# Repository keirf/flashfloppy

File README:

FlashFloppy
===========
Keir Fraser <keir.xen@gmail.com>
https://github.com/keirf/flashfloppy

This distribution contains FlashFloppy custom firmware for Gotek and
Gotek-compatible hardware.

FlashFloppy documentation and downloads:
  https://github.com/keirf/flashfloppy/wiki/

Supported Microcontrollers
--------------------------
FlashFloppy supports two types of STM32-like microcontroller:
 STM32F105 (and the compatible AT32F415)
   - 72MHz Cortex-M3, 128kB Flash, 64kB RAM (AT32F415: 32kB RAM)
 AT32F435
   - 288MHz Cortex-M4, 256kB Flash, 384kB RAM

If you want to know which type of MCU you have, you can open your Gotek and
read the writing on the square chip on your Gotek PCB.

Firmware Programming
--------------------
If programming a factory-fresh Gotek running factory firmware, you will need
to program a HEX or DFU firmware file as explained in the wiki, linked above.
These files are located in the hex/ and dfu/ folders respectively, and you
must use the correct file for your microcontroller:
 STM32F105, AT32F415
   - Use file "dfu/flashfloppy-at415-st105-<ver>.dfu" (or .hex equivalent)
 AT32F435
   - Use file "dfu/flashfloppy-at435-<ver>.dfu" (or .hex equivalent)

Firmware Update
---------------
Once FlashFloppy has been flashed to a device (using a HEX or DFU file),
further updates can be made via an Update file on a USB drive, as described
in the wiki.

To support older versions of the FlashFloppy bootloader, two types of
Update file are included in the distribution, distinguishable by name:
 FF_Gotek-*.upd: Legacy Update file
    - All STM32F105/AT32F415 devices
 flashfloppy-*.upd: Universal Update file
    - All AT32F435 devices
    - STM32F105/AT32F415 devices running a recent FlashFloppy bootloader

Each update format will only work with a device (and FlashFloppy bootloader)
that supports it. If you are unsure which to use, it is okay to copy both
Update file types to your USB drive: the bootloader will correctly load just
one of the Update file types that it supports.

Alternatively try one Update file at a time, and switch to the other type if
you see error E01 on the Gotek display.

Alternative Firmwares
---------------------
In the alt/ folder you will find (pairs of) Update files implementing
alternative firmwares. Most users can ignore these, and use only the
Update files in the root of the distribution.

The alternative firmwares include:
 * alt/bootloader: Updates your Gotek bootloader
   - WARNING: Proceed with caution. Read the Firmware Update page on the wiki.
 * alt/io-test: Test your Gotek I/O pins if you suspect a hardware fault
 * alt/quickdisk: QuickDisk emulation (see the wiki)
   - If you don't know what QuickDisk is, you don't need this firmware.
 * alt/logfile: Firmware with debug logging to FFLOG.TXT on the USB drive
   - Useful only for fault finding. Not for general use.

Redistribution
--------------
Source code, and all binary releases, are freely redistributable in
any form. Please see the the COPYING file included in this
distribution.

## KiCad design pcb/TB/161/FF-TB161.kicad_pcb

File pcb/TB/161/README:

FF-TB161
--------
KiCad project for schematic and 10cmx5cm single-board layout.
Can be opened in the KiCad project manager.

FF-TB161-bom.txt
----------------
Bill of materials for the above design, excluding pin headers
and socket strips.

FF-TB161-panel
--------------
Two-up 10x10cm panelisation of the above layout, with cutouts
and break-away mousebites. Should be opened directly in Pcbnew.

Generating Gerbers
------------------
Nothing special to note here. Some of these options are important to
follow, especially for the drill file.
Options:
 Plot footprint values
 Plot footprint references
 Exclude PCB edge layer from other layers
Gerber Options:
 Use Protel filename extensions
 Format: 4.6
Drill files:
 Drill Units:    Inches
 Zeros Format:   Suppress leading zeros
 Precision:      2:4
 Drill Options:  Minimal header
 Drill Origin:   Absolute

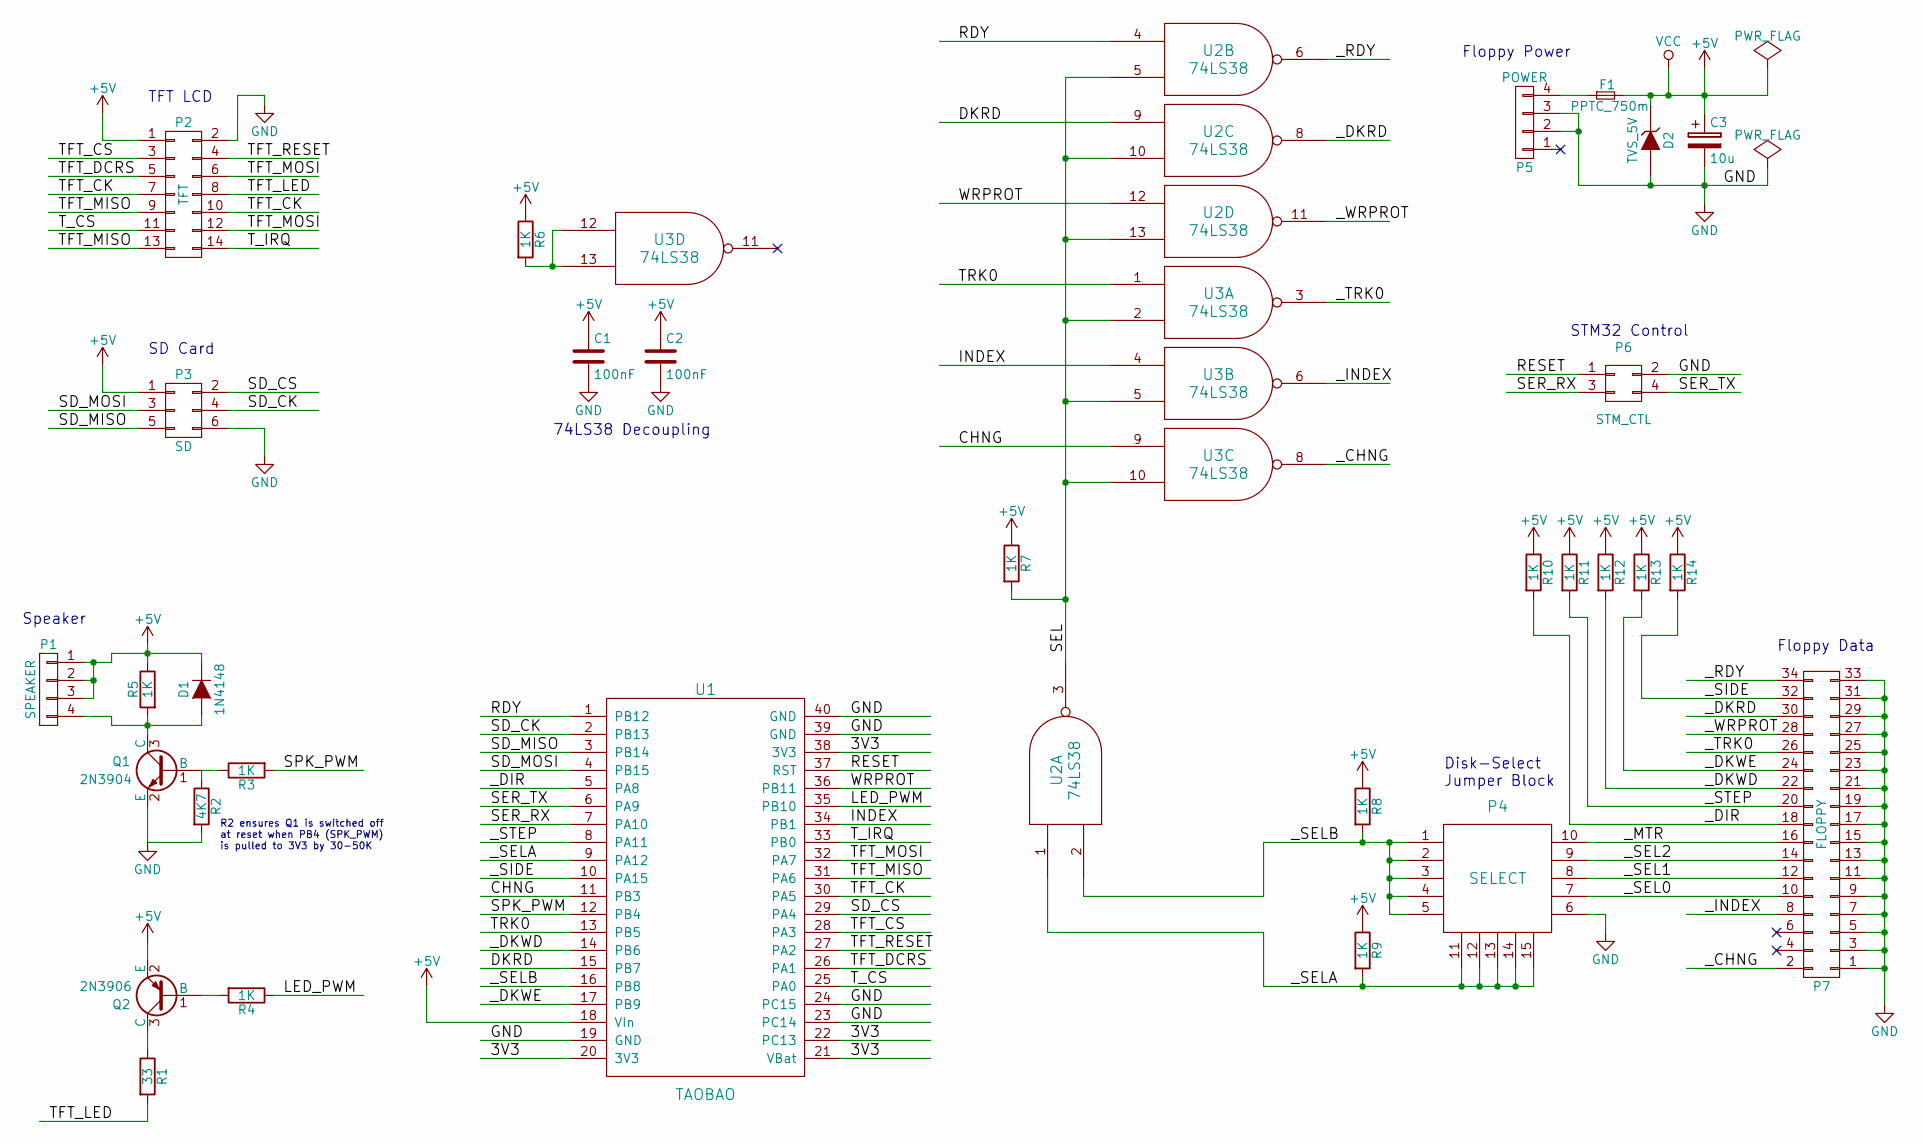
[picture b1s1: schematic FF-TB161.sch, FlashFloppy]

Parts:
C1, C2: 100nF; R_0805_HandSoldering
C3: 10u; C_3528
D1: 1N4148; MiniMELF_Handsoldering
D2: TVS_5V; D_SOD128
F1: PPTC_750m; R_0805_HandSoldering
P1: SPEAKER; Pin_Header_Straight_1x04
P2: TFT; Pin_Header_Straight_2x07
P3: SD; Pin_Header_Straight_2x03
P4: SELECT; Pin_Header_Straight_3x05
P5: POWER; Pin_Header_Straight_1x04
P6: STM_CTL; Pin_Header_Straight_2x02
P7: FLOPPY; Pin_Header_Straight_2x17
Q1: 2N3904; SOT-23_Handsoldering
Q2: 2N3906; SOT-23_Handsoldering
R1: 33; R_1206_HandSoldering
R2: 4K7; R_0805_HandSoldering
R3, R4, R5, R6, R7, R8, R9, R10, R11, R12, R13, R14: 1K; R_0805_HandSoldering
U1: TAOBAO; DIP-40_W15.24mm
U2, U3: 74LS38; SOIC-14_N

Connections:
+5V: C1.1, C2.1, C3.1, D1.1 (K), D2.1 (K), F1.2, P1.1, P1.2, P1.3, P2.1, P3.1, Q2.2 (E), R5.1, R6.1, R7.1, R8.1, R9.1, R10.1, R11.1, R12.1, R13.1, R14.1, U1.18 (VIn), U2.14 (VCC), U3.14 (VCC)
/3V3: U1.20 (3V3), U1.21 (VBat), U1.22 (PC13), U1.38 (3V3)
/CHNG: U1.11 (PB3), U3.9
/DKRD: U1.15 (PB7), U2.9
/INDEX: U1.34 (PB1), U3.4
/LED_PWM: R4.1, U1.35 (PB10)
/RDY: U1.1 (PB12), U2.4
/RESET: P6.1, U1.37 (RST)
/SD_CK: P3.4, U1.2 (PB13)
/SD_CS: P3.2, U1.29 (PA4)
/SD_MISO: P3.5, U1.3 (PB14)
/SD_MOSI: P3.3, U1.4 (PB15)
/SEL: R7.2, U2.3, U2.5, U2.10, U2.13, U3.2, U3.5, U3.10
/SER_RX: P6.3, U1.7 (PA10)
/SER_TX: P6.4, U1.6 (PA9)
/SPK_PWM: R3.2, U1.12 (PB4)
/TFT_CK: P2.7, P2.10, U1.30 (PA5)
/TFT_CS: P2.3, U1.28 (PA3)
/TFT_DCRS: P2.5, U1.26 (PA1)
/TFT_LED: P2.8, R1.2
/TFT_MISO: P2.9, P2.13, U1.31 (PA6)
/TFT_MOSI: P2.6, P2.12, U1.32 (PA7)
/TFT_RESET: P2.4, U1.27 (PA2)
/TRK0: U1.13 (PB5), U3.1
/T_CS: P2.11, U1.25 (PA0)
/T_IRQ: P2.14, U1.33 (PB0)
/WRPROT: U1.36 (PB11), U2.12
/_CHNG: P7.2, U3.8
/_DIR: P7.18, R10.2, U1.5 (PA8)
/_DKRD: P7.30, U2.8
/_DKWD: P7.22, R12.2, U1.14 (PB6)
/_DKWE: P7.24, R13.2, U1.17 (PB9)
/_INDEX: P7.8, U3.6
/_MTR: P4.10, P7.16
/_RDY: P7.34, U2.6
/_SEL0: P4.7, P7.10
/_SEL1: P4.8, P7.12
/_SEL2: P4.9, P7.14
/_SELA: P4.11, P4.12, P4.13, P4.14, P4.15, R9.2, U1.9 (PA12), U2.1
/_SELB: P4.1, P4.2, P4.3, P4.4, P4.5, R8.2, U1.16 (PB8), U2.2
/_SIDE: P7.32, R14.2, U1.10 (PA15)
/_STEP: P7.20, R11.2, U1.8 (PA11)
/_TRK0: P7.26, U3.3
/_WRPROT: P7.28, U2.11
GND: C1.2, C2.2, C3.2, D2.2 (A), P2.2, P3.6, P4.6, P5.2, P5.3, P6.2, P7.1, P7.3, P7.5, P7.7, P7.9, P7.11, P7.13, P7.15, P7.17, P7.19, P7.21, P7.23, P7.25, P7.27, P7.29, P7.31, P7.33, Q1.2 (E), R2.2, U1.19 (GND), U1.23 (PC14), U1.24 (PC15), U1.39 (GND), U1.40 (GND), U2.7 (GND), U3.7 (GND)
unnamed: D1.2 (A), P1.4, Q1.3 (C), R5.2
unnamed: F1.1, P5.4
unnamed: Q1.1 (B), R2.1, R3.1
unnamed: Q2.1 (B), R4.2
unnamed: Q2.3 (C), R1.1
unnamed: R6.2, U3.12, U3.13

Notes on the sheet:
Floppy Power
STM32 Control
Floppy Data
SD Card
TFT LCD
Speaker
Disk-Select Jumper Block
74LS38 Decoupling
R2 ensures Q1 is switched off at reset when PB4 (SPK_PWM) is pulled to 3V3 by 30-50K

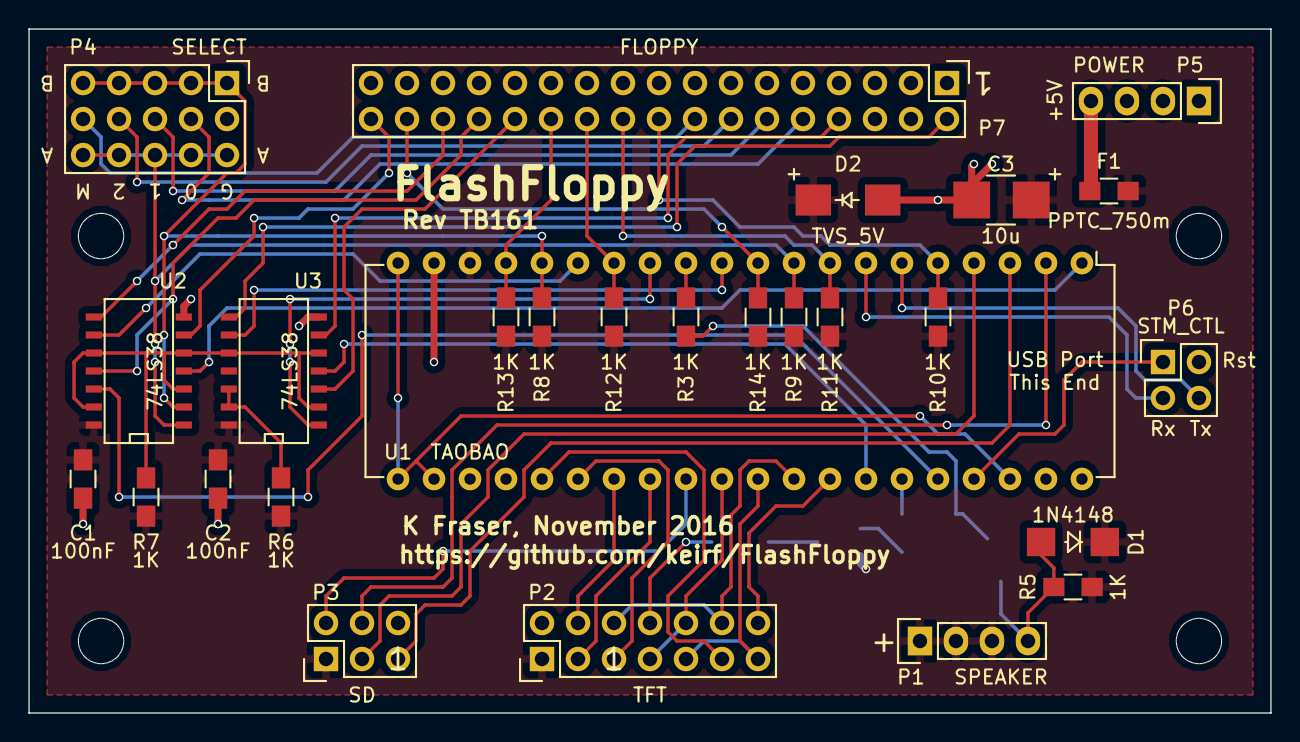
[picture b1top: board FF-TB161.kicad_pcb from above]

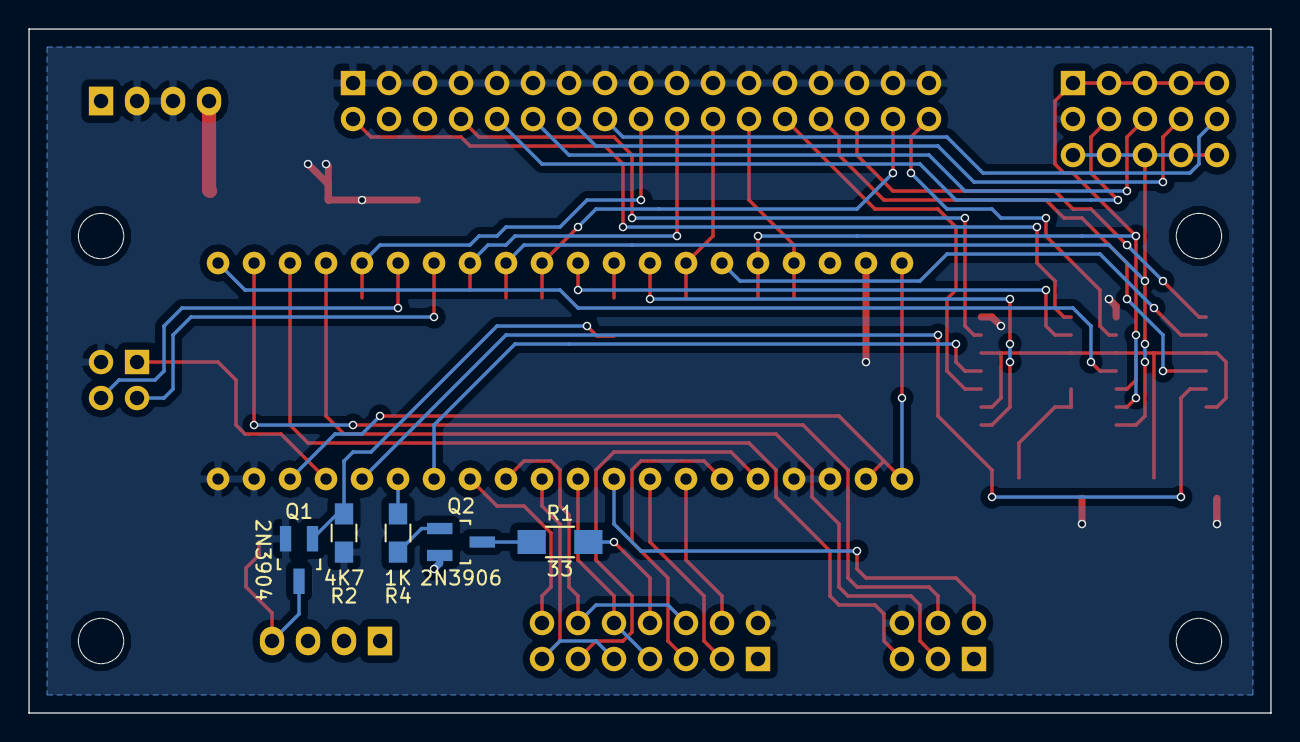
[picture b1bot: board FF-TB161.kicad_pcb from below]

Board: 2 copper layers, 87.6 x 48.3 mm, 32 parts (5 on the bottom side), 51 nets.

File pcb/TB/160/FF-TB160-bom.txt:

REF         PART DESCRIPTION                   RS ORDER
===         ================                   ========
F1          Bourns MF-PSMF075X-2 (0805)        691-7516
D1          LL4148 (MiniMELF, SOD-80)
D2          NXP PTVS5V0P1UP (SOD-128)          791-9052
            NXP PTVS5V0P1UTP (alternative)     791-9055
C1-C2       0.1uF (0805)                       390-990
C3          Vishay 293D106X9020B2TE3 (3528)    684-3904
Q1          MMBT3904 (SOT23)
Q2          MMBT3906 (SOT23)
U1          "Taobao" Mini STM32 (DIP40) [*]
U2-U3       74LS38 (SOIC14)
R1          33R,1%,1/4W (1206)
R3-R14      1K,5%,1/8W (0805)
P5          TE/AMP 171826-4 4-pin header       680-1225

[*] There are many variants of this Chinese design with informal names
    such as Red Pill, Blue Pill, JC-66, etc. Most have a pullup
    resistor on PA12: remove it or cut the connecting trace.

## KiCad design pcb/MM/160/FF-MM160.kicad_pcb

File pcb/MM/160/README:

This project was designed using a development snapshot of KiCad.

FF-MM160
--------
KiCad project for schematic and 10cmx5cm single-board layout.
Can be opened in the KiCad project manager.

FF-MM160-bom.txt
----------------
Bill of materials for the above design, excluding pin headers
and socket strips.

FF-MM160-panel
--------------
Two-up 10x10cm panelisation of the above layout, with cutouts
and break-away mousebites. Should be opened directly in Pcbnew.

Generating Gerbers
------------------
Nothing special to note here. Some of these options are important to
follow, especially for the drill file.
Options:
 Plot footprint values
 Plot footprint references
 Exclude PCB edge layer from other layers
Gerber Options:
 Use Protel filename extensions
 Format: 4.6
Drill files:
 Drill Units:    Inches
 Zeros Format:   Suppress leading zeros
 Precision:      2:4
 Drill Options:  Minimal header
 Drill Origin:   Absolute

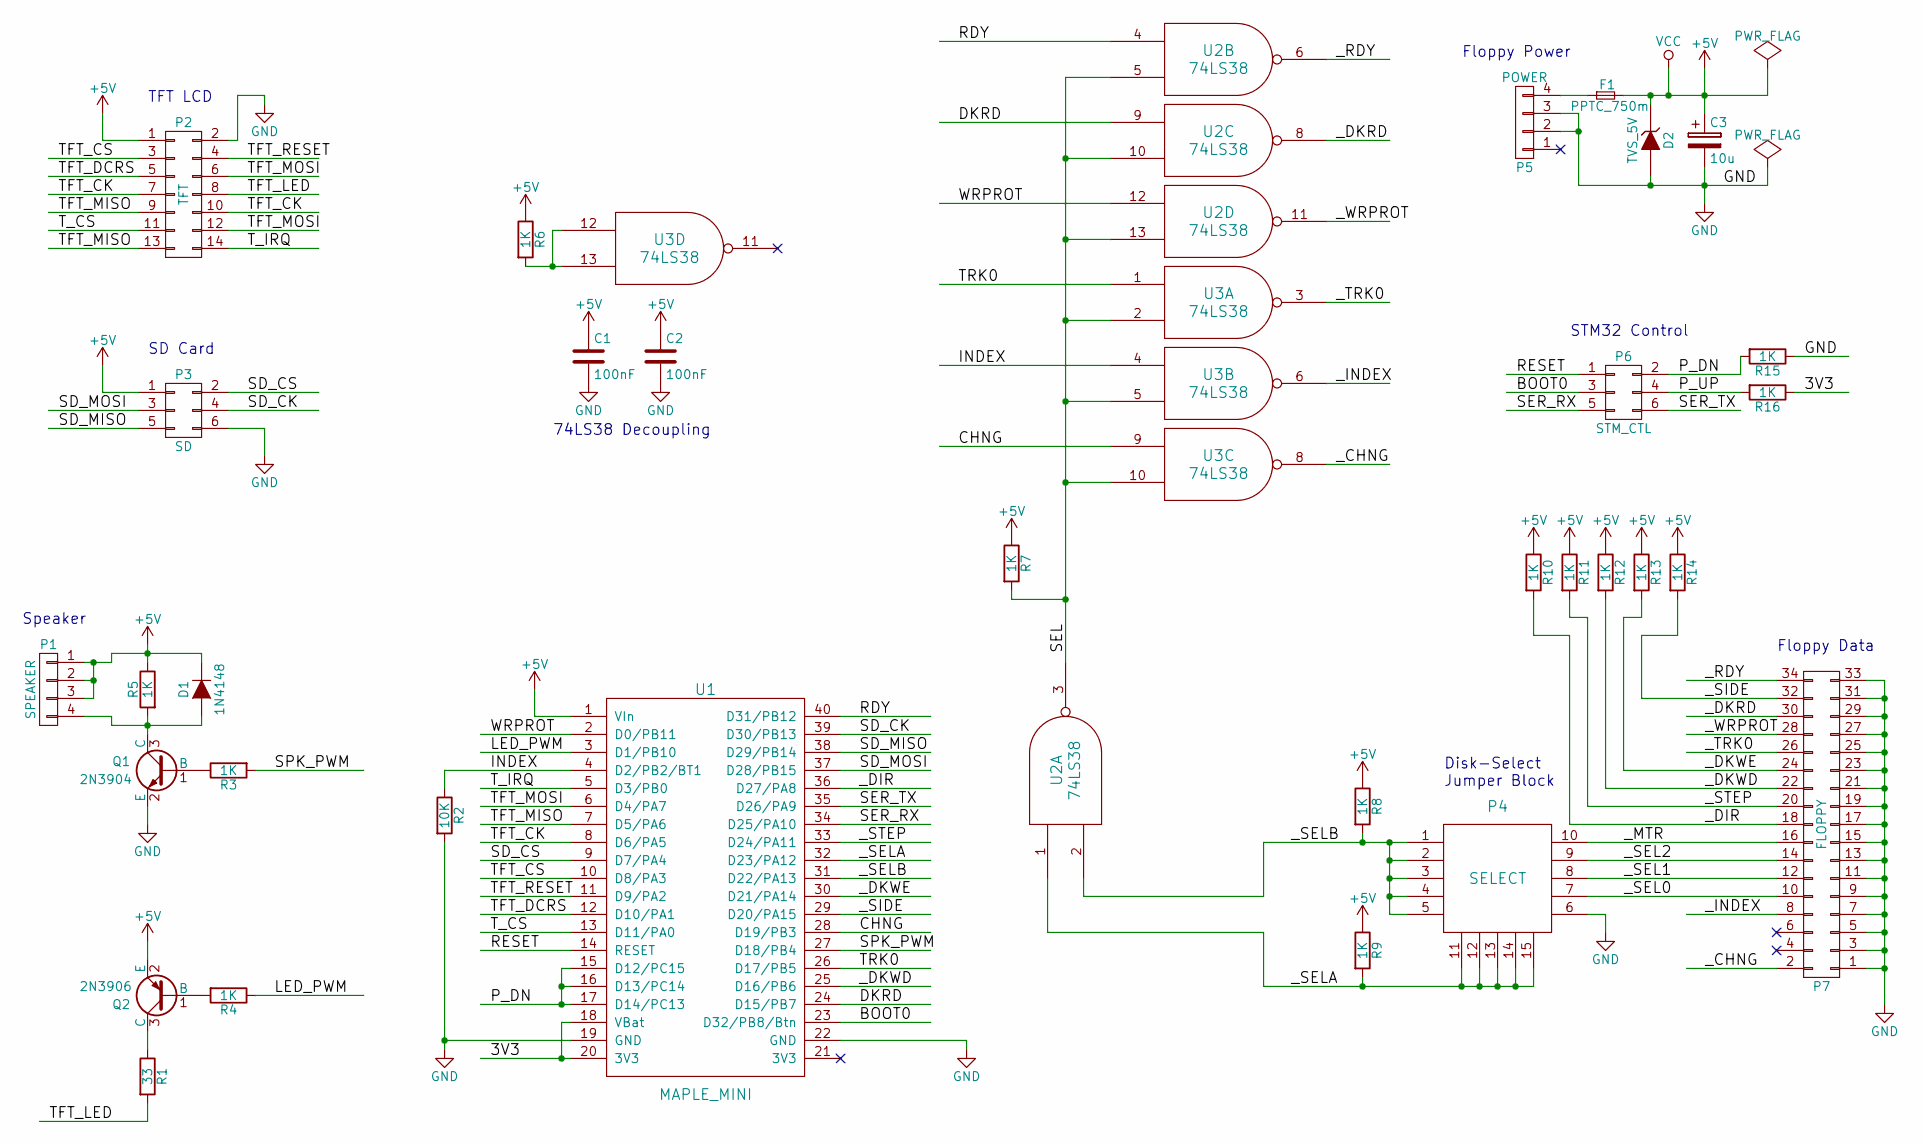
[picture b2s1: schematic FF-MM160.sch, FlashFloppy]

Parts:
C1, C2: 100nF; R_0805_HandSoldering
C3: 10u; C_3528
D1: 1N4148; MiniMELF_Handsoldering
D2: TVS_5V; D_SOD128
F1: PPTC_750m; R_0805_HandSoldering
P1: SPEAKER; Pin_Header_Straight_1x04
P2: TFT; Pin_Header_Straight_2x07
P3: SD; Pin_Header_Straight_2x03
P4: SELECT; Pin_Header_Straight_3x05
P5: POWER; Pin_Header_Straight_1x04
P6: STM_CTL; Pin_Header_Straight_2x03
P7: FLOPPY; Pin_Header_Straight_2x17
Q1: 2N3904; SOT-23_Handsoldering
Q2: 2N3906; SOT-23_Handsoldering
R1: 33; R_1206_HandSoldering
R2: 10K; R_0805_HandSoldering
R3, R4, R5, R6, R7, R8, R9, R10, R11, R12, R13, R14, R15, R16: 1K; R_0805_HandSoldering
U1: MAPLE_MINI; DIP-40_W15.24mm
U2, U3: 74LS38; SOIC-14_N

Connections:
+5V: C1.1, C2.1, C3.1, D1.1 (K), D2.1 (K), F1.2, P1.1, P1.2, P1.3, P2.1, P3.1, Q2.2 (E), R5.1, R6.1, R7.1, R8.1, R9.1, R10.1, R11.1, R12.1, R13.1, R14.1, U1.1 (VIn), U2.14 (VCC), U3.14 (VCC)
/3V3: R16.1, U1.18 (VBat), U1.20 (3V3)
/BOOT0: P6.3, U1.23 (D32/PB8/Btn)
/CHNG: U1.28 (D19/PB3), U3.9
/DKRD: U1.24 (D15/PB7), U2.9
/INDEX: R2.1, U1.4 (D2/PB2/BT1), U3.4
/LED_PWM: R4.1, U1.3 (D1/PB10)
/P_DN: P6.2, R15.2, U1.15 (D12/PC15), U1.16 (D13/PC14), U1.17 (D14/PC13)
/P_UP: P6.4, R16.2
/RDY: U1.40 (D31/PB12), U2.4
/RESET: P6.1, U1.14 (RESET)
/SD_CK: P3.4, U1.39 (D30/PB13)
/SD_CS: P3.2, U1.9 (D7/PA4)
/SD_MISO: P3.5, U1.38 (D29/PB14)
/SD_MOSI: P3.3, U1.37 (D28/PB15)
/SEL: R7.2, U2.3, U2.5, U2.10, U2.13, U3.2, U3.5, U3.10
/SER_RX: P6.5, U1.34 (D25/PA10)
/SER_TX: P6.6, U1.35 (D26/PA9)
/SPK_PWM: R3.2, U1.27 (D18/PB4)
/TFT_CK: P2.7, P2.10, U1.8 (D6/PA5)
/TFT_CS: P2.3, U1.10 (D8/PA3)
/TFT_DCRS: P2.5, U1.12 (D10/PA1)
/TFT_LED: P2.8, R1.2
/TFT_MISO: P2.9, P2.13, U1.7 (D5/PA6)
/TFT_MOSI: P2.6, P2.12, U1.6 (D4/PA7)
/TFT_RESET: P2.4, U1.11 (D9/PA2)
/TRK0: U1.26 (D17/PB5), U3.1
/T_CS: P2.11, U1.13 (D11/PA0)
/T_IRQ: P2.14, U1.5 (D3/PB0)
/WRPROT: U1.2 (D0/PB11), U2.12
/_CHNG: P7.2, U3.8
/_DIR: P7.18, R10.2, U1.36 (D27/PA8)
/_DKRD: P7.30, U2.8
/_DKWD: P7.22, R12.2, U1.25 (D16/PB6)
/_DKWE: P7.24, R13.2, U1.30 (D21/PA14)
/_INDEX: P7.8, U3.6
/_MTR: P4.10, P7.16
/_RDY: P7.34, U2.6
/_SEL0: P4.7, P7.10
/_SEL1: P4.8, P7.12
/_SEL2: P4.9, P7.14
/_SELA: P4.11, P4.12, P4.13, P4.14, P4.15, R9.2, U1.32 (D23/PA12), U2.1
/_SELB: P4.1, P4.2, P4.3, P4.4, P4.5, R8.2, U1.31 (D22/PA13), U2.2
/_SIDE: P7.32, R14.2, U1.29 (D20/PA15)
/_STEP: P7.20, R11.2, U1.33 (D24/PA11)
/_TRK0: P7.26, U3.3
/_WRPROT: P7.28, U2.11
GND: C1.2, C2.2, C3.2, D2.2 (A), P2.2, P3.6, P4.6, P5.2, P5.3, P7.1, P7.3, P7.5, P7.7, P7.9, P7.11, P7.13, P7.15, P7.17, P7.19, P7.21, P7.23, P7.25, P7.27, P7.29, P7.31, P7.33, Q1.2 (E), R2.2, R15.1, U1.19 (GND), U1.22 (GND), U2.7 (GND), U3.7 (GND)
unnamed: D1.2 (A), P1.4, Q1.3 (C), R5.2
unnamed: F1.1, P5.4
unnamed: Q1.1 (B), R3.1
unnamed: Q2.1 (B), R4.2
unnamed: Q2.3 (C), R1.1
unnamed: R6.2, U3.12, U3.13

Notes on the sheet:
Floppy Power
STM32 Control
Floppy Data
SD Card
TFT LCD
Speaker
Disk-Select Jumper Block
74LS38 Decoupling

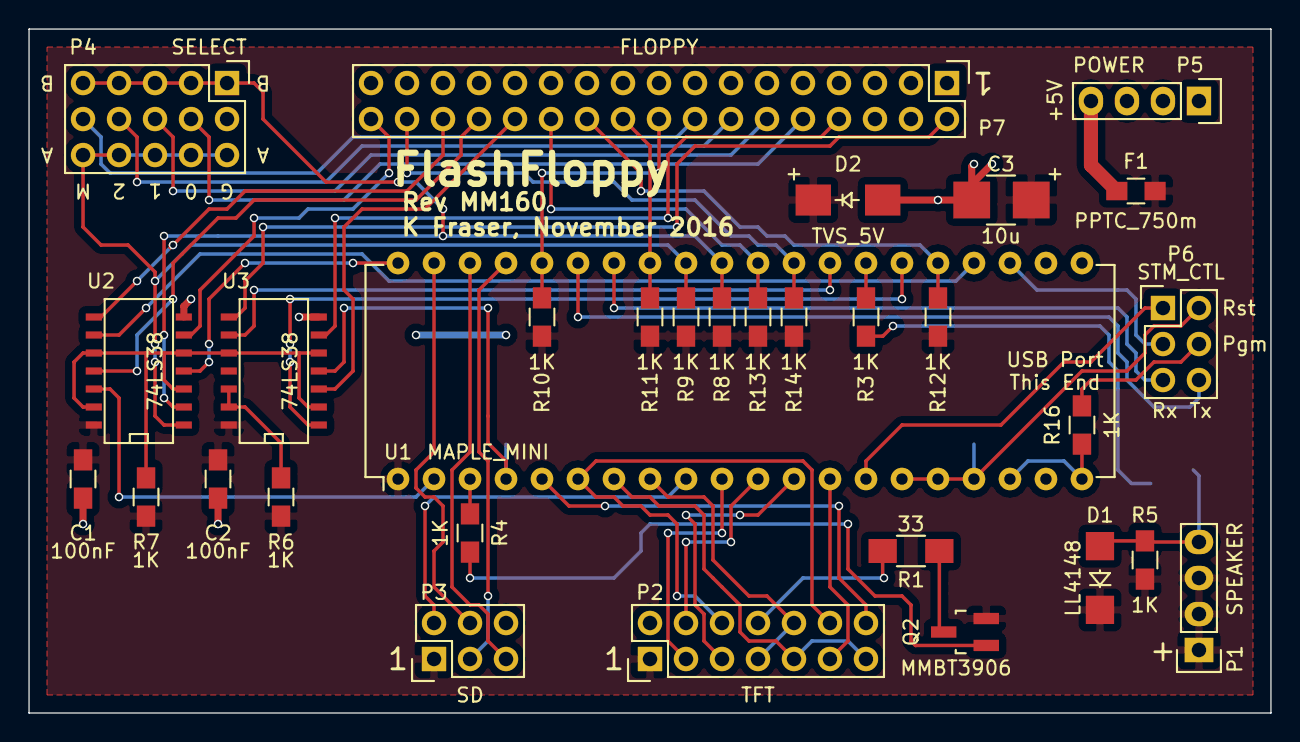
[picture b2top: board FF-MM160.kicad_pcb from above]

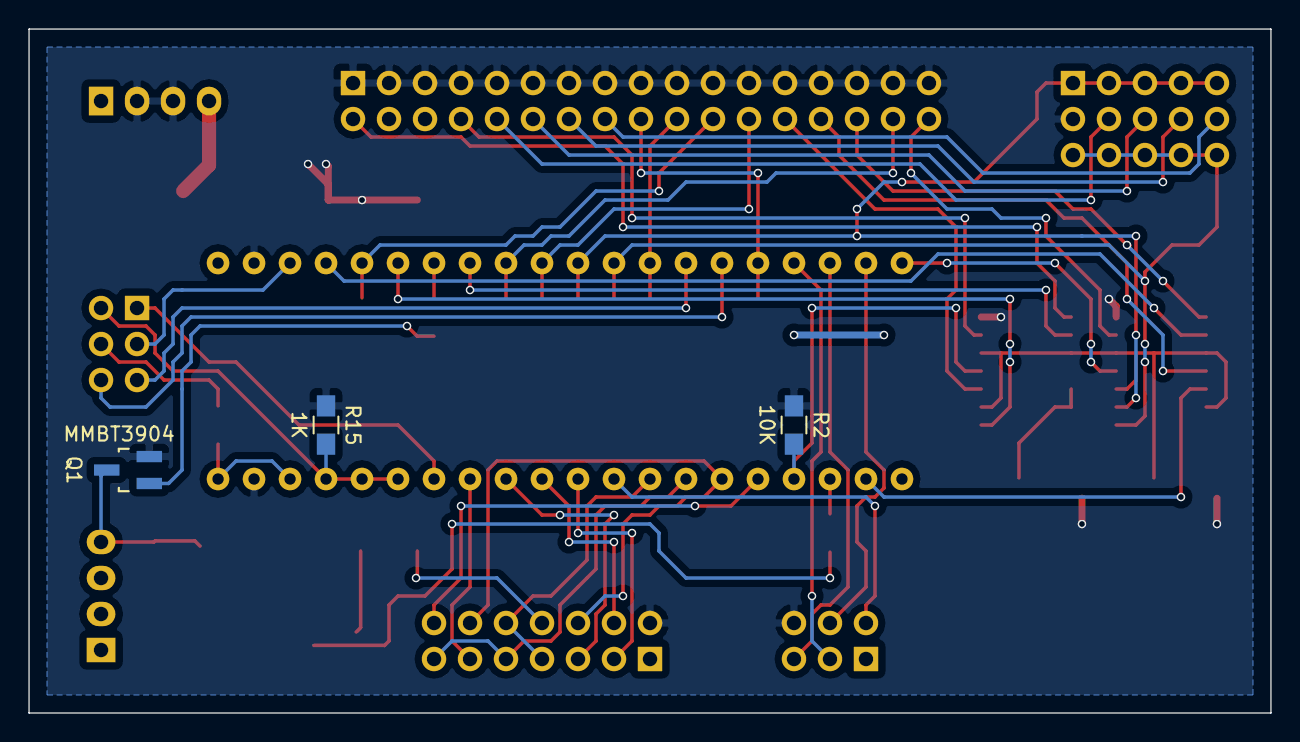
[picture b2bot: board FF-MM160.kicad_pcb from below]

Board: 2 copper layers, 87.6 x 48.3 mm, 34 parts (3 on the bottom side), 54 nets.

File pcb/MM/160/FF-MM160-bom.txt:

REF         PART DESCRIPTION                   RS ORDER
===         ================                   ========
F1          Bourns MF-PSMF075X-2 (0805)        691-7516
D1          LL4148 (MiniMELF, SOD-80)
D2          NXP PTVS5V0P1UP (SOD-128)          791-9052
            NXP PTVS5V0P1UTP (alternative)     791-9055
C1-C2       0.1uF (0805)                       390-990
C3          Vishay 293D106X9020B2TE3 (3528)    684-3904
Q1          MMBT3904 (SOT23)
Q2          MMBT3906 (SOT23)
U1          Maple Mini STM32 (DIP40)
U2-U3       74LS38 (SOIC14)
R1          33R,1%,1/4W (1206)
R2          10K,5%,1/8W (0805)
R3-R16      1K,5%,1/8W (0805)
P5          TE/AMP 171826-4 4-pin header       680-1225

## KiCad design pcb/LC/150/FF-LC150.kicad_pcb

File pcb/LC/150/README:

This project was designed using a development snapshot of KiCad.

FF-LC150
--------
KiCad project for schematic and 10cmx5cm single-board layout.
Can be opened in the KiCad project manager.

FF-LC150-bom.txt
----------------
Bill of materials for the above design, excluding pin headers
and socket strips.

FF-LC150-panel
--------------
Two-up 10x10cm panelisation of the above layout, with cutouts
and break-away mousebites. Should be opened directly in Pcbnew.

Generating Gerbers
------------------
Nothing special to note here. Some of these options are important to
follow, especially for the drill file.
Options:
 Plot footprint values
 Plot footprint references
 Exclude PCB edge layer from other layers
Gerber Options:
 Use Protel filename extensions
 Format: 4.6
Drill files:
 Drill Units:    Inches
 Zeros Format:   Suppress leading zeros
 Precision:      2:4
 Drill Options:  Minimal header
 Drill Origin:   Absolute

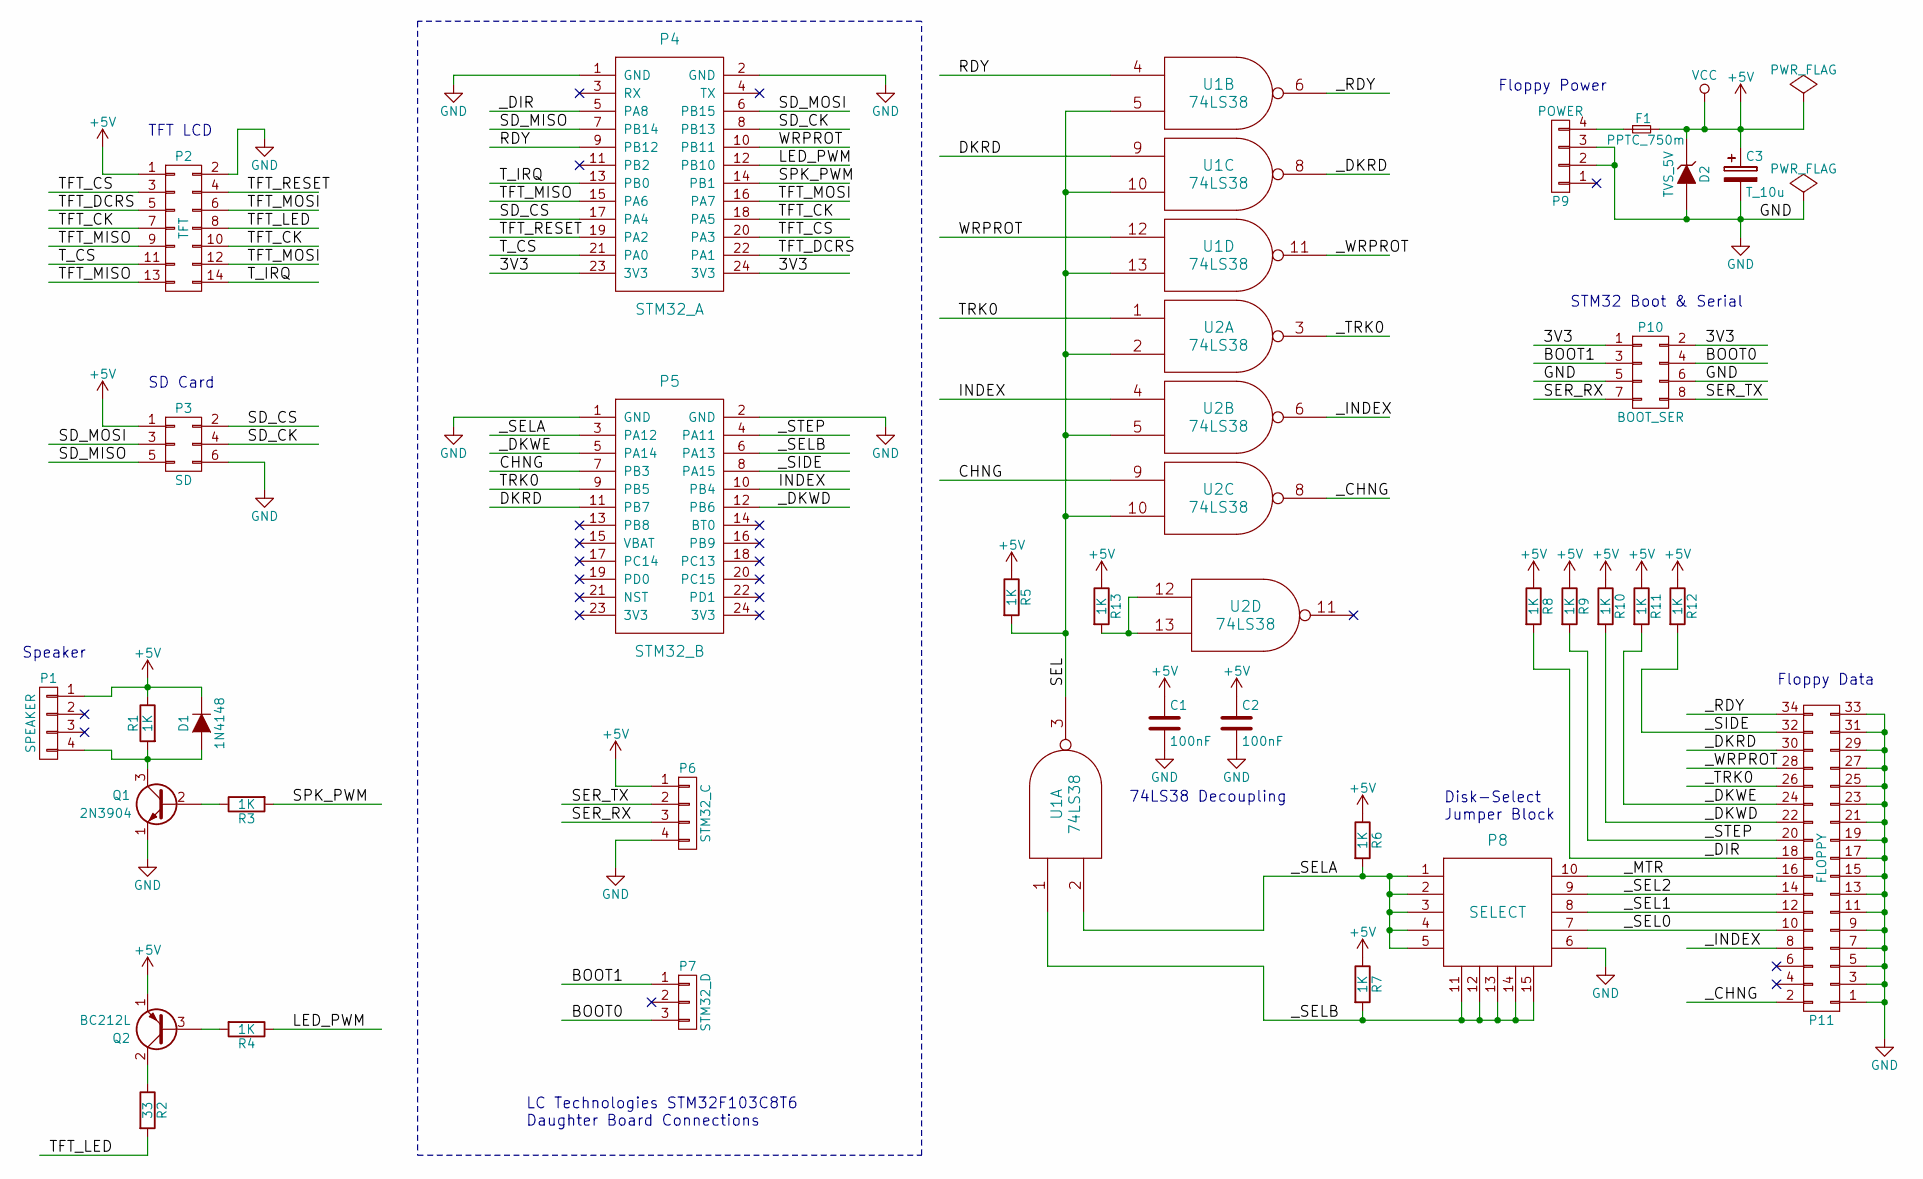
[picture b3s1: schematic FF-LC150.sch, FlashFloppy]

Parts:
C1, C2: 100nF; C_Disc_D6_P5
C3: T_10u; TantalC_SizeB_EIA-3528_HandSoldering
D1: 1N4148; Diode_DO-35_SOD27_Horizontal_RM10
D2: TVS_5V; Diode-Universal-SMA-SMB_Handsoldering
F1: PPTC_750m; Fuse_SMD1206_HandSoldering
P1: SPEAKER; Pin_Header_Straight_1x04
P2: TFT; Pin_Header_Straight_2x07
P3: SD; Pin_Header_Straight_2x03
P4: STM32_A; Socket_Strip_Straight_2x12
P5: STM32_B; Socket_Strip_Straight_2x12
P6: STM32_C; Socket_Strip_Straight_1x04
P7: STM32_D; Socket_Strip_Straight_1x03
P8: SELECT; Pin_Header_Straight_3x05
P9: POWER; Pin_Header_Straight_1x04
P10: BOOT_SER; Pin_Header_Straight_2x04
P11: FLOPPY; Pin_Header_Straight_2x17
Q1: 2N3904; TO-92_Inline_Narrow_Oval
Q2: BC212L; TO-92_Molded_Wide
R1, R3, R4, R5, R6, R7, R8, R9, R10, R11, R12, R13: 1K; Resistor_Horizontal_RM10mm
R2: 33; Resistor_Horizontal_RM10mm
U1, U2: 74LS38; DIP-14_W7.62mm

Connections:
+5V: C1.1, C2.1, C3.1, D1.1 (K), D2.1 (K), F1.2, P1.1, P2.1, P3.1, P6.1, Q2.1 (E), R1.1, R5.1, R6.1, R7.1, R8.1, R9.1, R10.1, R11.1, R12.1, R13.1, U1.14 (VCC), U2.14 (VCC)
/3V3: P4.23 (3V3), P4.24 (3V3), P10.1, P10.2
/BOOT0: P7.3, P10.4
/BOOT1: P7.1, P10.3
/CHNG: P5.7 (PB3), U2.9
/DKRD: P5.11 (PB7), U1.9
/INDEX: P5.10 (PB4), U2.4
/LED_PWM: P4.12 (PB10), R4.1
/RDY: P4.9 (PB12), U1.4
/SD_CK: P3.4, P4.8 (PB13)
/SD_CS: P3.2, P4.17 (PA4)
/SD_MISO: P3.5, P4.7 (PB14)
/SD_MOSI: P3.3, P4.6 (PB15)
/SEL: R5.2, U1.3, U1.5, U1.10, U1.13, U2.2, U2.5, U2.10
/SER_RX: P6.3, P10.7
/SER_TX: P6.2, P10.8
/SPK_PWM: P4.14 (PB1), R3.2
/TFT_CK: P2.7, P2.10, P4.18 (PA5)
/TFT_CS: P2.3, P4.20 (PA3)
/TFT_DCRS: P2.5, P4.22 (PA1)
/TFT_LED: P2.8, R2.2
/TFT_MISO: P2.9, P2.13, P4.15 (PA6)
/TFT_MOSI: P2.6, P2.12, P4.16 (PA7)
/TFT_RESET: P2.4, P4.19 (PA2)
/TRK0: P5.9 (PB5), U2.1
/T_CS: P2.11, P4.21 (PA0)
/T_IRQ: P2.14, P4.13 (PB0)
/WRPROT: P4.10 (PB11), U1.12
/_CHNG: P11.2, U2.8
/_DIR: P4.5 (PA8), P11.18, R8.2
/_DKRD: P11.30, U1.8
/_DKWD: P5.12 (PB6), P11.22, R10.2
/_DKWE: P5.5 (PA14), P11.24, R11.2
/_INDEX: P11.8, U2.6
/_MTR: P8.10, P11.16
/_RDY: P11.34, U1.6
/_SEL0: P8.7, P11.10
/_SEL1: P8.8, P11.12
/_SEL2: P8.9, P11.14
/_SELA: P5.3 (PA12), P8.1, P8.2, P8.3, P8.4, P8.5, R6.2, U1.2
/_SELB: P5.6 (PA13), P8.11, P8.12, P8.13, P8.14, P8.15, R7.2, U1.1
/_SIDE: P5.8 (PA15), P11.32, R12.2
/_STEP: P5.4 (PA11), P11.20, R9.2
/_TRK0: P11.26, U2.3
/_WRPROT: P11.28, U1.11
GND: C1.2, C2.2, C3.2, D2.2 (A), P2.2, P3.6, P4.1 (GND), P4.2 (GND), P5.1 (GND), P5.2 (GND), P6.4, P8.6, P9.2, P9.3, P10.5, P10.6, P11.1, P11.3, P11.5, P11.7, P11.9, P11.11, P11.13, P11.15, P11.17, P11.19, P11.21, P11.23, P11.25, P11.27, P11.29, P11.31, P11.33, Q1.1 (E), U1.7 (GND), U2.7 (GND)
unnamed: D1.2 (A), P1.4, Q1.3 (C), R1.2
unnamed: F1.1, P9.4
unnamed: Q1.2 (B), R3.1
unnamed: Q2.2 (C), R2.1
unnamed: Q2.3 (B), R4.2
unnamed: R13.2, U2.12, U2.13

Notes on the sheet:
LC Technologies STM32F103C8T6 Daughter Board Connections
Floppy Power
STM32 Boot & Serial
Floppy Data
SD Card
TFT LCD
Speaker
Disk-Select Jumper Block
74LS38 Decoupling

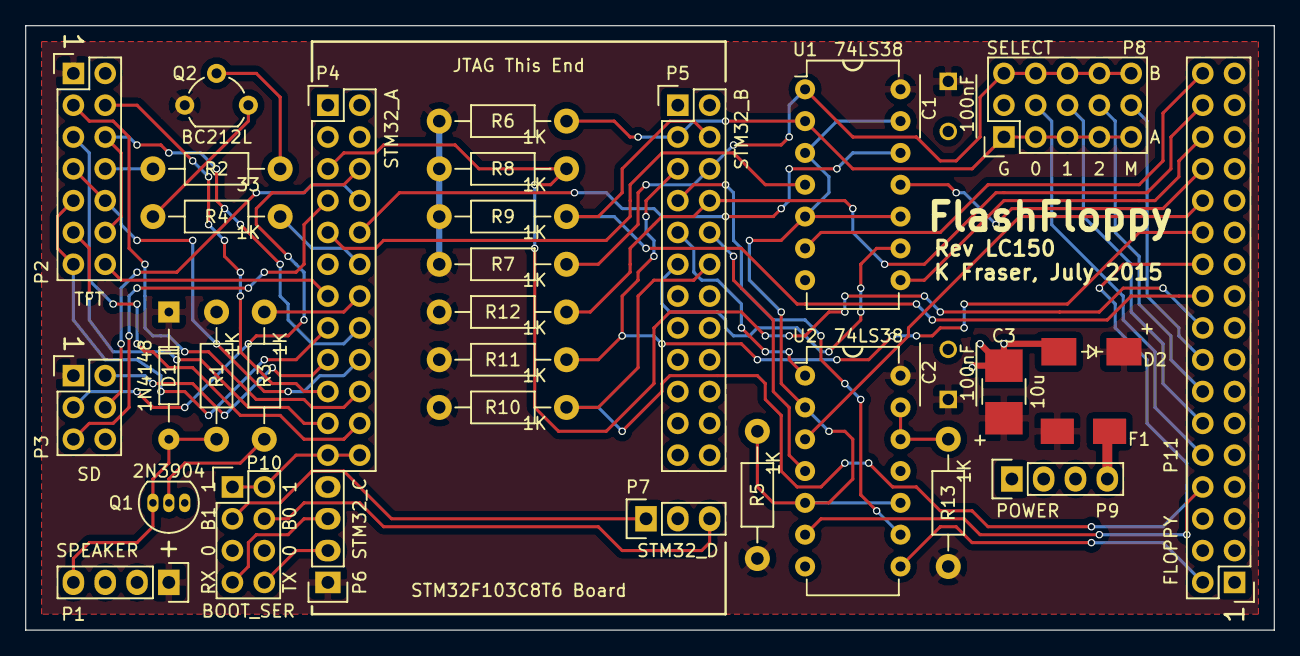
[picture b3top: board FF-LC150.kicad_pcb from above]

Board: 2 copper layers, 99.7 x 48.3 mm, 34 parts (0 on the bottom side), 52 nets.
